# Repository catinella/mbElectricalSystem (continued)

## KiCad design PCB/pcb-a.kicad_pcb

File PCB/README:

#-------------------------------------------------------------------------------------------------------------------------------
   __  __       _             _     _ _          _____ _           _        _           _   ____            _                 
  |  \/  | ___ | |_ ___  _ __| |__ (_) | _____  | ____| | ___  ___| |_ _ __(_) ___ __ _| | / ___| _   _ ___| |_ ___ _ __ ___  
  | |\/| |/ _ \| __/ _ \| '__| '_ \| | |/ / _ \ |  _| | |/ _ \/ __| __| '__| |/ __/ _` | | \___ \| | | / __| __/ _ \ '_ ` _ \ 
  | |  | | (_) | || (_) | |  | |_) | |   <  __/ | |___| |  __/ (__| |_| |  | | (_| (_| | |  ___) | |_| \__ \ ||  __/ | | | | |
  |_|  |_|\___/ \__\___/|_|  |_.__/|_|_|\_\___| |_____|_|\___|\___|\__|_|  |_|\___\__,_|_| |____/ \__, |___/\__\___|_| |_| |_|
                                                                                                  |___/                       
#-------------------------------------------------------------------------------------------------------------------------------

Description:
	This folder contains all files you need to get you own PCB.

Files:
	LICENSE.txt                 This project is covered by the GPL-3. Please, read that file for further information
	Makefile                    It allow you to create the files (es. Gebber) needed to produce the PCB (KiCAD-7)
	kicad_symbols               This folder contains all components definitions not provided by KiCAD by default
	pcb-a                       All files belong to the PCB-a
	pcb-b                       All files belong to the PCB-b
	starter_key_plug            Schema to show the key-plug internals

Internals:
	The power astage was originally implemented with BJT transistors, but as my colleague usually say "we are no more in the
	90' age".  For this reason I have designed a new PCB-B using MOSfet technology

	+---------+--------------------------------+--------------------------------+
	| BC817   | VCE=0.2V IC=800mA              | BJT NPN                        |
	| IRF4905 | RDS=20mOhm ID=50A VGS=[-2..-4] | P-Channel MOSfet enhancement   |
	+---------+--------------------------------+--------------------------------+

Devices building:
	About the PCBs creation I have used the MD srl company service. So, in order to create a copy, you can contact the company
	(https://www.mdsrl.it) and use the following order numbers, it will allow you to save some money.
		+-----------------+-----------+----------+---------------+
		|       PCB       |   GIT TAG | MD order |     Price     |
		+-----------------+-----------+----------+---------------+
		| pcb-a.kicad_pcb | r-2.2.4-0 |  81552   | 18.9 euro * 2 |
		+-----------------+-----------+--------------------------+
		| pcb-b.kicad_pcb | r-2.2.4-b |  882813  | 36.5 euro * 2 |
		+-----------------+-----------+--------------------------+

	PCB building details:
	=====================
	In order to get a more vibrations resistant circuit,  I suggest you to print it on a 3.2mm high plate
	
	[!] It you are using Linux, you too, remember that the PCB building company will require you a ZIP file (not GZIP).
	    So, after the fabric-files generation use the following command to create the zip file:
	    	zip -r <archive name> <data folder name>

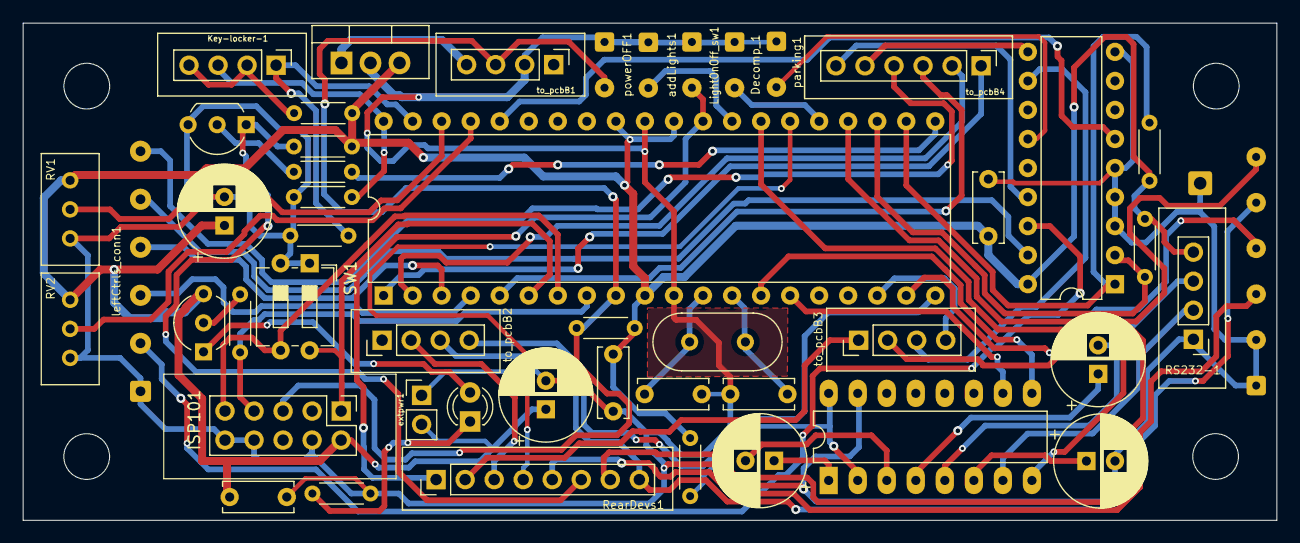
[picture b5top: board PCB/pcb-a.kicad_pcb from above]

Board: 2 copper layers, 109.7 x 43.5 mm, 49 parts (0 on the bottom side), 58 nets.

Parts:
C1: 100uf; CP_Radial_D8.0mm_P2.50mm
C2, C9, C10: 100nF; C_Disc_D6.0mm_W2.5mm_P5.00mm
C3: 15pf; C_Disc_D6.0mm_W2.5mm_P5.00mm
C4: 15pF; C_Disc_D6.0mm_W2.5mm_P5.00mm
C5, C6, C8: 1uf; CP_Radial_D8.0mm_P2.50mm
C7: 50uf; CP_Radial_D8.0mm_P2.50mm
D1: LED; LED_D3.0mm
Decomp_1: Conn_01x02; SolderWire-0.15sqmm_1x02_P4mm_D0.5mm_OD1.5mm
ISP101: ISP10 Connector; PinHeader_2x05_P2.54mm_Vertical
Key-locker-1: Conn_01x04; PinHeader_1x04_P2.54mm_Vertical
LightOnOff_sw1: Conn_01x02; SolderWire-0.15sqmm_1x02_P4mm_D0.5mm_OD1.5mm
Q1: BC327; TO-92_Inline_Wide
Q3: BC337; TO-92_Inline_Wide
R1, R3, R4: 1K; R_Axial_DIN0204_L3.6mm_D1.6mm_P5.08mm_Horizontal
R2, R7, R8: 10K; R_Axial_DIN0204_L3.6mm_D1.6mm_P5.08mm_Horizontal
R5, R10: 2K; R_Axial_DIN0204_L3.6mm_D1.6mm_P5.08mm_Horizontal
R6: 100K; R_Axial_DIN0204_L3.6mm_D1.6mm_P5.08mm_Horizontal
R9: 5K; R_Axial_DIN0204_L3.6mm_D1.6mm_P5.08mm_Horizontal
R11: 20; R_Axial_DIN0204_L3.6mm_D1.6mm_P5.08mm_Horizontal
RS232-1: Conn_01x04; PinHeader_1x04_P2.54mm_Vertical
RV1, RV2: 10K; Potentiometer_Bourns_3296W_Vertical
RearDevs1: Conn_01x08; PinHeader_1x08_P2.54mm_Vertical
SW1: config; SW_DIP_SPSTx02_Slide_6.7x6.64mm_W7.62mm_P2.54mm_LowProfile
U1: MCP23008-xP; DIP-18_W7.62mm
U2: MAX232I; CERDIP-16_W7.62mm_SideBrazed_LongPads
U3: L7805; TO-220-3_Vertical
U4: ATmega16L-8P; DIP-40_W15.24mm
Y1: 8Mhz; Crystal_HC49-U_Vertical
addLights1: Conn_01x02; SolderWire-0.15sqmm_1x02_P4mm_D0.5mm_OD1.5mm
extpwr1: Conn_01x02; PinHeader_1x02_P2.54mm_Vertical
leftCtrls-faston1: Conn_01x01; SolderWire-0.5sqmm_1x01_D0.9mm_OD2.1mm
leftCtrls_conn1: Conn_01x06; SolderWire-0.25sqmm_1x06_P4.2mm_D0.65mm_OD1.7mm
parking1: Conn_01x02; SolderWire-0.15sqmm_1x02_P4mm_D0.5mm_OD1.5mm
powerOFF1: Conn_01x02; SolderWire-0.15sqmm_1x02_P4mm_D0.5mm_OD1.5mm
rightCtrls_conn1: Conn_01x06; SolderWire-0.15sqmm_1x06_P4mm_D0.5mm_OD1.5mm
to_pcbB1, to_pcbB2, to_pcbB3: Conn_01x04; PinHeader_1x04_P2.54mm_Vertical
to_pcbB4: Conn_01x06; PinHeader_1x06_P2.54mm_Vertical

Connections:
5V: C1.1, C2.1, C7.1, C9.1, C10.2, ISP101.2, Q1.3 (E), R1.1, R2.1, R5.1, R6.2, R10.1, R11.1, RS232-1.4, RV1.1, RV2.1, U1.18 (VDD), U3.3 (OUT), U4.10 (VCC), U4.30 (AVCC), U4.32 (AREF), extpwr1.2
GND: C1.2, C2.2, C3.2, C4.2, C7.2, C8.2, C9.2, C10.1, Decomp_1.1, ISP101.4, ISP101.8, ISP101.10, LightOnOff_sw1.1, Q3.3 (E), R3.2, R4.2, R9.2, RS232-1.1, RV1.3, RV2.3, SW1.1, SW1.2, U1.3 (A2), U1.4 (A1), U1.5 (A0), U1.9 (VSS), U2.15 (GND), U3.2 (GND), U4.11 (GND), U4.31 (GND), addLights1.1, extpwr1.1, leftCtrls-faston1.1, leftCtrls_conn1.1, parking1.1, powerOFF1.1, rightCtrls_conn1.1, rightCtrls_conn1.2, to_pcbB1.2
unnamed: D1.2 (A), Q1.1 (C)
unnamed: D1.1 (K), R9.1
unnamed: ISP101.1, SW1.4, U4.6 (PB5)
unnamed: ISP101.7, R8.2, U4.8 (PB7)
unnamed: ISP101.9, SW1.3, U4.7 (PB6)
unnamed: Key-locker-1.2, Key-locker-1.4, R1.2
unnamed: Q1.2 (B), R8.1
unnamed: Q3.2 (B), R7.1
unnamed: RS232-1.2, U2.7 (T2OUT)
unnamed: RS232-1.3, U2.8 (R2IN)
unnamed: R10.2, U1.1 (SCL), U4.22 (PC0)
unnamed: R5.2, U1.2 (SDA), U4.23 (PC1)
unnamed: U1.6 (~RESET), U4.36 (PA4)
unnamed: C5.1, U2.1 (C1+)
unnamed: C5.2, U2.3 (C1-)
unnamed: C6.1, U2.4 (C2+)
unnamed: C6.2, U2.5 (C2-)
unnamed: R11.2, U2.2 (VS+), U2.16 (VCC)
unnamed: C8.1, U2.6 (VS-)
unnamed: U3.1 (IN), to_pcbB1.4
unnamed: RV1.2, U4.38 (PA2)
unnamed: RV2.2, U4.37 (PA3)
unnamed: C3.1, U4.13 (XTAL1), Y1.2
unnamed: C4.1, U4.12 (XTAL2), Y1.1
c_RS232_RXD: U2.9 (R2OUT), U4.14 (PD0)
c_RS232_TXT: U2.10 (T2IN), U4.15 (PD1)
c_brakeSwitch: RearDevs1.5, rightCtrls_conn1.3
c_engineOFF: RearDevs1.8, rightCtrls_conn1.5, to_pcbB2.3
c_horn: leftCtrls_conn1.6, to_pcbB4.4
c_leftArrow: RearDevs1.2, to_pcbB3.1
c_neutral: RearDevs1.7, U4.27 (PC5), to_pcbB3.2
c_rearLight: LightOnOff_sw1.2, RearDevs1.1, U4.29 (PC7)
c_rightArrow: RearDevs1.3, to_pcbB2.2
c_startEngine: Q3.1 (C), R6.1, RearDevs1.6
i_Vx1: Key-locker-1.3, R3.1, U4.40 (PA0)
i_Vx2: Key-locker-1.1, R4.1, U4.39 (PA1)
i_addLight: U4.28 (PC6), addLights1.2
i_bykeStand: RearDevs1.4, U4.26 (PC4)
i_decompr: Decomp_1.2, U4.25 (PC3)
i_downLight: U4.4 (PB3), leftCtrls_conn1.3
i_engineON: U4.24 (PC2), rightCtrls_conn1.6
i_leftArrow: U1.16 (GP6), leftCtrls_conn1.2
i_parking: U1.13 (GP3), parking1.2
i_powerOFF: ISP101.5, R2.2, U4.9 (~RESET), powerOFF1.2, to_pcbB1.3
i_rightArrow: U1.17 (GP7), leftCtrls_conn1.5
i_startButton: U4.19 (PD5), rightCtrls_conn1.4
i_upLight: U4.3 (PB2), leftCtrls_conn1.4
o_addLight: U4.5 (PB4), to_pcbB4.3
o_downLight: U4.1 (PB0), to_pcbB4.1
o_engineON: U4.20 (PD6), to_pcbB2.4
o_engineReady: U1.11 (GP1), to_pcbB3.3
o_keepAlive: U4.18 (PD4), to_pcbB3.4
o_leftArrow: U1.15 (GP5), to_pcbB4.6
o_rightArrow: U1.10 (GP0), to_pcbB4.5
o_startEngine: R7.2, U4.21 (PD7)
o_upLight: U4.2 (PB1), to_pcbB4.2

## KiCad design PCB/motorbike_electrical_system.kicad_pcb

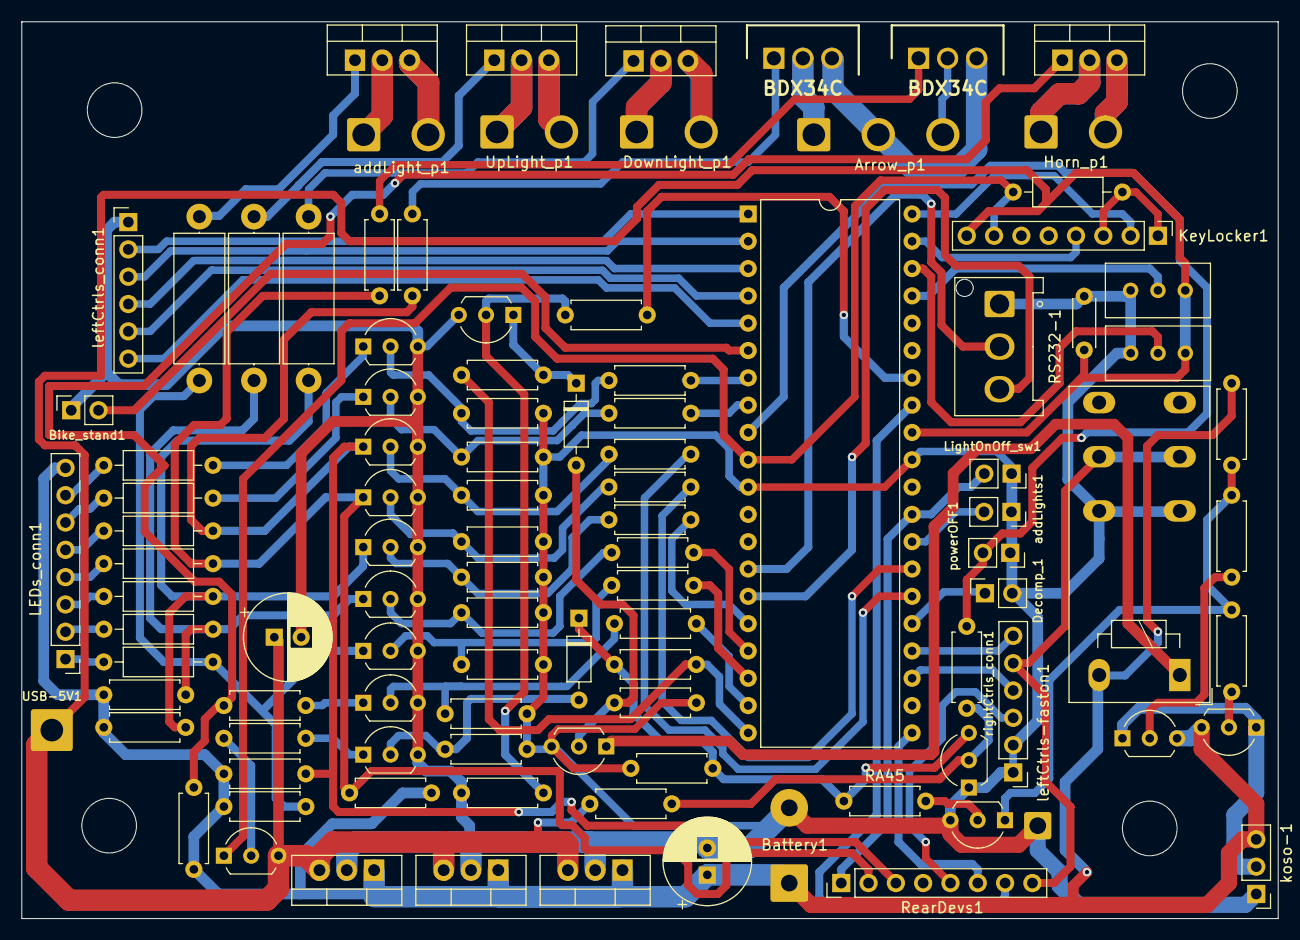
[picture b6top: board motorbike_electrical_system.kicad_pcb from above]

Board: 2 copper layers, 116.9 x 83.4 mm, 104 parts (0 on the bottom side), 91 nets.

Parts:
Arrow_p1: Conn_01x03; SolderWire-1.5sqmm_1x03_P6mm_D1.7mm_OD3mm
Battery1: Conn_01x02; SolderWire-0.75sqmm_1x02_P7mm_D1.25mm_OD3.5mm
Bike_stand1: Conn_01x02; PinSocket_1x02_P2.54mm_Vertical
C1, C9: C_Polarized_Small; CP_Radial_D8.0mm_P2.50mm
C2: 100nF; C_Disc_D4.3mm_W1.9mm_P5.00mm
D3, D4: 2V; D_DO-35_SOD27_P7.62mm_Horizontal
Decomp_1: Conn_01x02; PinSocket_1x02_P2.54mm_Vertical
DownLight_p1: Conn_01x02; SolderWire-1.5sqmm_1x02_P6mm_D1.7mm_OD3mm
Horn_p1: Conn_01x02; SolderWire-1.5sqmm_1x02_P6mm_D1.7mm_OD3mm
IC2, IC3: BDX34C; TO270P460X1020X2008-3P
K1: RT42xxxx; Relay_DPDT_Schrack-RT2-FormC_RM5mm
KeyLocker1: Conn_01x08; PinHeader_1x08_P2.54mm_Vertical
LEDs_conn1: Conn_01x08; PinHeader_1x08_P2.54mm_Vertical
LightOnOff_sw1: Conn_01x02; PinSocket_1x02_P2.54mm_Vertical
Q1, Q2, Q14, Q15: D45VH10; TO-220-3_Vertical
Q3, Q4, Q5, Q6, Q7, Q8, Q9, Q10, Q11, Q13, Q16, Q17: BC337; TO-92L_Inline_Wide
Q12, Q18, Q19, Q20: BC327; TO-92L_Inline_Wide
R1: 1K; R_Axial_DIN0207_L6.3mm_D2.5mm_P10.16mm_Horizontal
RA1, RA2, RA3, RA4, RA5, RA6, RA9: 0; R_Axial_DIN0207_L6.3mm_D2.5mm_P10.16mm_Horizontal
RA7: 1K; R_Axial_DIN0207_L6.3mm_D2.5mm_P7.62mm_Horizontal
RA8, RA41: 4K; R_Axial_DIN0207_L6.3mm_D2.5mm_P7.62mm_Horizontal
RA10, RA11, RA12: 240; R_Axial_DIN0414_L11.9mm_D4.5mm_P15.24mm_Horizontal
RA13, RA14: 8K; R_Axial_DIN0207_L6.3mm_D2.5mm_P7.62mm_Horizontal
RA15: 240; R_Axial_DIN0207_L6.3mm_D2.5mm_P7.62mm_Horizontal
RA16, RA17, RA18, RA19, RA20, RA21, RA22, RA23: 5K; R_Axial_DIN0207_L6.3mm_D2.5mm_P7.62mm_Horizontal
RA24, RA25, RA26, RA27, RA28, RA30, RA31, RA32, RA34, RA35, RA36, RA37, RA38, RA39, RA40, RA42, RA43, RA44, RA48, RA49: 100K; R_Axial_DIN0207_L6.3mm_D2.5mm_P7.62mm_Horizontal
RA29, RA33, RA45: 10K; R_Axial_DIN0207_L6.3mm_D2.5mm_P7.62mm_Horizontal
RA46, RA47: 3K; R_Axial_DIN0207_L6.3mm_D2.5mm_P7.62mm_Horizontal
RS232-1: Conn_01x03; Hirose_DF63M-3P-3.96DSA_1x03_P3.96mm_Vertical
RV1, RV2: 10K; Potentiometer_Bourns_3296W_Vertical
RearDevs1: Conn_01x08; PinHeader_1x08_P2.54mm_Vertical
U1, U2, U3: L7805; TO-220-3_Vertical
U4: ATmega16L-8P; DIP-40_W15.24mm
USB-5V1: Conn_01x01; SolderWire-1.5sqmm_1x01_D1.7mm_OD3.9mm
UpLight_p1: Conn_01x02; SolderWire-1.5sqmm_1x02_P6mm_D1.7mm_OD3mm
addLight_p1: Conn_01x02; SolderWire-1.5sqmm_1x02_P6mm_D1.7mm_OD3mm
addLights1: Conn_01x02; PinSocket_1x02_P2.54mm_Vertical
koso-1: Conn_01x03; PinHeader_1x03_P2.54mm_Vertical
leftCtrls-faston1: Conn_01x01; SolderWire-0.75sqmm_1x01_D1.25mm_OD2.3mm
leftCtrls_conn1: Conn_01x06; PinHeader_1x06_P2.54mm_Vertical
powerOFF1: Conn_01x02; PinSocket_1x02_P2.54mm_Vertical
rightCtrls_conn1: Conn_01x06; PinHeader_1x06_P2.54mm_Vertical

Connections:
+5V: C1.1, C2.1, KeyLocker1.8, Q12.3 (E), RA44.1, RV1.1, RV2.1, U1.3 (OUT), U2.3 (OUT), U3.3 (OUT), U4.32 (AREF), USB-5V1.1
+12V: Battery1.1, C9.1, K1.A2, LEDs_conn1.8, Q19.3 (E), Q20.3 (E), RA24.1, RA25.1, RA26.1, RA27.1, RA28.1, RA42.1, RA49.2, U1.1 (IN), U2.1 (IN), U3.1 (IN), koso-1.3
GND: Battery1.2, Bike_stand1.1, C1.2, C2.2, C9.2, Decomp_1.2, K1.12, K1.22, LightOnOff_sw1.1, Q3.3 (E), Q4.3 (E), Q5.3 (E), Q6.3 (E), Q7.3 (E), Q8.3 (E), Q9.3 (E), Q10.3 (E), Q11.3 (E), Q13.3 (E), Q16.3 (E), Q17.3 (E), Q18.1 (C), RA30.2, RA31.2, RA32.2, RA34.2, RA35.2, RA36.2, RA37.2, RA38.2, RA39.2, RA40.2, RA43.1, RA48.2, RS232-1.1, RV1.3, RV2.3, U1.2 (GND), U2.2 (GND), U3.2 (GND), U4.11 (GND), U4.31 (GND), addLights1.1, koso-1.1, leftCtrls-faston1.1, leftCtrls_conn1.1, powerOFF1.1, rightCtrls_conn1.1, rightCtrls_conn1.2
unnamed: Arrow_p1.1, IC3.2 (C)
unnamed: Arrow_p1.2, IC2.3 (E), IC3.3 (E)
unnamed: Arrow_p1.3, IC2.2 (C)
unnamed: D3.1 (K), Q17.1 (C), RA41.1
unnamed: D3.2 (A), Q13.2 (B), RA31.1
unnamed: D4.1 (K), Q18.3 (E), RA8.1, RA45.1, RA48.1
unnamed: D4.2 (A), Q11.2 (B), RA30.1
unnamed: DownLight_p1.1, Q14.2
unnamed: DownLight_p1.2, Q14.3
unnamed: Horn_p1.1, Q15.2
unnamed: Horn_p1.2, Q15.3
unnamed: IC2.1 (B), RA13.2
unnamed: IC3.1 (B), RA14.2
unnamed: K1.A1, Q13.1 (C)
unnamed: KeyLocker1.1, KeyLocker1.3, R1.2
unnamed: LEDs_conn1.1, RA1.2
unnamed: LEDs_conn1.2, RA2.2
unnamed: LEDs_conn1.3, RA3.2
unnamed: LEDs_conn1.4, RA4.2
unnamed: LEDs_conn1.5, RA5.2
unnamed: LEDs_conn1.6, RA6.2
unnamed: LEDs_conn1.7, RA9.2
unnamed: Q1.1, RA10.2
unnamed: Q1.2, addLight_p1.1
unnamed: Q1.3, addLight_p1.2
unnamed: Q2.1, RA11.2
unnamed: Q2.2, UpLight_p1.1
unnamed: Q2.3, UpLight_p1.2
unnamed: Q3.1 (C), RA1.1, RA10.1, RA24.2
unnamed: Q3.2 (B), RA22.1, RA34.1
unnamed: Q4.1 (C), RA2.1, RA11.1, RA25.2
unnamed: Q4.2 (B), RA21.1, RA35.1
unnamed: Q5.1 (C), RA3.1, RA12.1, RA26.2
unnamed: Q5.2 (B), RA20.1, RA36.1
unnamed: Q6.2 (B), RA19.1, RA37.1
unnamed: Q7.2 (B), RA18.1, RA38.1
unnamed: Q8.1 (C), RA6.1
unnamed: Q8.2 (B), RA17.1, RA39.1
unnamed: Q9.1 (C), RA15.1
unnamed: Q9.2 (B), RA23.1, RA32.1
unnamed: Q10.1 (C), RA9.1
unnamed: Q10.2 (B), RA16.1, RA40.1
unnamed: Q11.1 (C), RA7.1
unnamed: Q12.2 (B), RA7.2
unnamed: Q14.1, RA12.2
unnamed: Q15.1, RA15.2, RA42.2
unnamed: Q16.1 (C), RA46.2, RA47.2, RA49.1
unnamed: Q16.2 (B), RA45.2
unnamed: Q17.2 (B), RA33.1, RA43.2
unnamed: Q18.2 (B), RA29.1, RA44.2
unnamed: Q19.1 (C), Q20.1 (C), koso-1.2
unnamed: Q19.2 (B), RA46.1
unnamed: Q20.2 (B), RA47.1
unnamed: RS232-1.2, U4.14 (PD0)
unnamed: RV1.2, U4.38 (PA2)
unnamed: RV2.2, U4.37 (PA3)
unnamed: RS232-1.3, U4.15 (PD1)
c_brakeSwitch: RearDevs1.5, rightCtrls_conn1.3
c_engineOFF: K1.11, K1.21, RearDevs1.8, rightCtrls_conn1.5
c_leftArrow: Q6.1 (C), RA4.1, RA13.1, RA27.2, RearDevs1.2
c_rearLight: LightOnOff_sw1.2, RearDevs1.1, U4.29 (PC7)
c_rightArrow: Q7.1 (C), RA5.1, RA14.1, RA28.2, RearDevs1.3
i_Vx1: KeyLocker1.2, U4.40 (PA0)
i_Vx2: KeyLocker1.4, U4.39 (PA1)
i_addLight: U4.28 (PC6), addLights1.2
i_bykeStand: Bike_stand1.2, U4.6 (PB5)
i_decompr: Decomp_1.1, U4.25 (PC3)
i_downLight: U4.2 (PB1), leftCtrls_conn1.3
i_engineON: U4.24 (PC2), rightCtrls_conn1.6
i_horn: U4.5 (PB4), leftCtrls_conn1.6
i_leftArrow: U4.1 (PB0), leftCtrls_conn1.2
i_neutral: RearDevs1.7, U4.33 (PA7)
i_powerOFF: RA29.2, U4.9 (~RESET), powerOFF1.2
i_rightArrow: U4.4 (PB3), leftCtrls_conn1.5
i_startButton: U4.23 (PC1), rightCtrls_conn1.4
i_upLight: U4.3 (PB2), leftCtrls_conn1.4
o_addLight: RA22.2, U4.18 (PD4)
o_downLight: RA20.2, U4.16 (PD2)
o_engineOFF: RA33.2, U4.34 (PA6)
o_engineReady: RA16.2, U4.7 (PB6)
o_horn: RA23.2, U4.19 (PD5)
o_keepAlive: RA8.2, RA41.2, U4.20 (PD6)
o_leftArrow: RA19.2, U4.27 (PC5)
o_neutral: RA17.2, U4.8 (PB7)
o_rightArrow: RA18.2, U4.26 (PC4)
o_startEngine: RearDevs1.6, U4.21 (PD7)
o_upLight: RA21.2, U4.17 (PD3)
tempPower: KeyLocker1.7, Q12.1 (C), R1.1, U4.10 (VCC)

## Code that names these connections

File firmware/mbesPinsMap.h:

/*------------------------------------------------------------------------------------------------------------------------------
//
//  __  __       _             _     _ _          _____ _           _        _           _   ____            _                 
// |  \/  | ___ | |_ ___  _ __| |__ (_) | _____  | ____| | ___  ___| |_ _ __(_) ___ __ _| | / ___| _   _ ___| |_ ___ _ __ ___  
// | |\/| |/ _ \| __/ _ \| '__| '_ \| | |/ / _ \ |  _| | |/ _ \/ __| __| '__| |/ __/ _` | | \___ \| | | / __| __/ _ \ '_ ` _ \
// | |  | | (_) | || (_) | |  | |_) | |   <  __/ | |___| |  __/ (__| |_| |  | | (_| (_| | |  ___) | |_| \__ \ ||  __/ | | | | |
// |_|  |_|\___/ \__\___/|_|  |_.__/|_|_|\_\___| |_____|_|\___|\___|\__|_|  |_|\___\__,_|_| |____/ \__, |___/\__\___|_| |_| |_|
//                                                                                                 |___/                       
//
// File:   mbesPinsMap.h
//
// Author: Silvano Catinella <catinella@yahoo.com>
//
//
//	Symbol description:
//		+---------------+------------------+-----------------------------------------------------+
//		|     Symbol    |    Plug/link     |      Description                                    |
//		+---------------+------------------+-----------------------------------------------------+
//		| i_VX1         | resistors-key    | first voltage value                                 |
//		| i_VX2         |                  | second  "       "                                   |
//		+---------------+------------------+-----------------------------------------------------+
//		| i_VY1         |  internal link   | first voltage reference                             |
//		| i_VY2         |                  | second  "         "                                 |
//		+---------------+------------------+-----------------------------------------------------+
//		| i_NEUTRAL     | from gearbox     | it is 0 when the gear is in neutral position        |
//		+---------------+------------------+-----------------------------------------------------+
//		| i_DECOMPRESS  | from decompress. | it is 0 when decompressor has been pushes           |
//		+---------------+------------------+-----------------------------------------------------+
//		| o_KEEPALIVE   | internal only    | it keeps the system on when you unplug the key      |
//		+---------------+------------------+-----------------------------------------------------+
//		| i_LEFTARROW   |                  | left turn blinking indicator switch                 |
//		| i_CLUTCH      |                  |                                     |
//		| i_UPLIGHT     | left controls    | dazzling beam command                               |
//		| i_RIGHTARROW  |                  | right turn blinking indicator switch                |
//		| i_HORN        |                  | horn button                                         |
//		+---------------+------------------+-----------------------------------------------------+
//		| i_BIKESTAND   | from bikestand   | it is 0 when the bike is placed on the stand        |
//		+---------------+------------------+-----------------------------------------------------+
//		| i_STARTBUTTON |                  | the tipical motorbike engine start button           |
//		| i_BRAKESWITCH | right controls   | the switch on the front brake command               |
//		| i_ENGINEON    |                  | the on/off engine switch in on-position             |
//		+---------------+------------------+-----------------------------------------------------+
//		| i_ADDLIGHT    | from ext. switch | additional high power light                         |
//		+---------------+------------------+-----------------------------------------------------+
//		| i_LIGHTONOFF  | from ext. switch | it turns on the normal lights (low/dazzling beam)   |
//		+---------------+------------------+-----------------------------------------------------+
//		| o_STARTENGINE | rear mtb. side   | it activates the (NO) engine-relay                  |
//		+---------------+------------------+-----------------------------------------------------+
//		| o_ENGINEREADY |                  |                                                     |
//		| o_NEUTRAL     |                  |                                                     |
//		| o_RIGHTARROW  |   cockpit LED    |                                                     |
//		| o_LEFTARROW   | indicators and   |                                                     |
//		| o_DOWNLIGHT   |    services      |                                                     |
//		| o_UPLIGHT     |                  |                                                     |
//		| o_ADDLIGHT    |                  |                                                     |
//		| o_HORN        |                  |                                                     |
//		+---------------+------------------+-----------------------------------------------------+
//
// License:
//	Copyright (C) 2023 Silvano Catinella <catinella@yahoo.com>
//
//	This program is free software: you can redistribute it and/or modify it under the terms of the GNU General Public
//	License as published by the Free Software Foundation, either version 3 of the License, or (at your option) any later
//	version.
//
//	This program is distributed in the hope that it will be useful, but WITHOUT ANY WARRANTY; without even the implied
//	warranty of MERCHANTABILITY or FITNESS FOR A PARTICULAR PURPOSE. See the GNU General Public License for more details.
//
//	You should have received a copy of the GNU General Public License along with this program. If not, see
//		<https://www.gnu.org/licenses/gpl-3.0.txt>.
//
------------------------------------------------------------------------------------------------------------------------------*/
#ifndef MBESPINSMAP
#define MBESPINSMAP

//
// PINs declaration
//

#define i_VX1          "A0"
#define i_VX2          "A1"
#define i_VY1          "A2"
#define i_VY2          "A3"
#define o_MCPDEVRESET  "A4"
// ==== available ==== "A5"
#define i_SELCONFIG    "A6"
#define i_CONFIG       "A7"


#define o_DOWNLIGHT    "B0"
#define o_UPLIGHT      "B1"
#define i_UPLIGHT      "B2"
#define i_CLUTCH       "B3"
#define o_ADDLIGHT     "B4"
// ===== ISP =====     "B5"
// ===== ISP =====     "B6"
// ===== ISP =====     "B7"


// ====== I2C ======   "C0"
// ====== I2C ======   "C1"
#define i_ENGINEON     "C2"
#define i_DECOMPRESS   "C3"
#define i_BYKESTAND    "C4"
#define i_NEUTRAL      "C5"
#define i_ADDLIGHT     "C6"
#define i_LIGHTONOFF   "C7"


// === RXD UART ===    "D0"
// === TXD UART ===    "D1"
// ==== available ==== "D2"
// ==== available ==== "D3"
#define o_KEEPALIVE    "D4"
#define i_STARTBUTTON  "D5"
#define o_ENGINEON     "D6"
#define o_STARTENGINE  "D7"


#define o_RIGHTARROW   "00"
#define o_ENGINEREADY  "01"
#define o_NEUTRAL      "02"
#define o_HORN         "03"
#define i_HORN         "04"
#define o_LEFTARROW    "05"
#define i_LEFTARROW    "06"
#define i_RIGHTARROW   "07"


// Number of used analog input
#define ACHANS_NUMBER   4

#endif

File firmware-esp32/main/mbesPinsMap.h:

/*------------------------------------------------------------------------------------------------------------------------------
//
//  __  __       _             _     _ _          _____ _           _        _           _   ____            _                 
// |  \/  | ___ | |_ ___  _ __| |__ (_) | _____  | ____| | ___  ___| |_ _ __(_) ___ __ _| | / ___| _   _ ___| |_ ___ _ __ ___  
// | |\/| |/ _ \| __/ _ \| '__| '_ \| | |/ / _ \ |  _| | |/ _ \/ __| __| '__| |/ __/ _` | | \___ \| | | / __| __/ _ \ '_ ` _ \
// | |  | | (_) | || (_) | |  | |_) | |   <  __/ | |___| |  __/ (__| |_| |  | | (_| (_| | |  ___) | |_| \__ \ ||  __/ | | | | |
// |_|  |_|\___/ \__\___/|_|  |_.__/|_|_|\_\___| |_____|_|\___|\___|\__|_|  |_|\___\__,_|_| |____/ \__, |___/\__\___|_| |_| |_|
//                                                                                                 |___/                       
//
// File:   mbesPinsMap.h
//
// Author: Silvano Catinella <catinella@yahoo.com>
//
//
//	Symbol description:
//		+---------------+------------------+-----------------------------------------------------+
//		|     Symbol    |    Plug/link     |      Description                                    |
//		+---------------+------------------+-----------------------------------------------------+
//		| i_VX1         | resistors-key    | first voltage value                                 |
//		| i_VX2         |                  | second  "       "                                   |
//		+---------------+------------------+-----------------------------------------------------+
//		| i_NEUTRAL     | from gearbox     | it is 0 when the gear is in neutral position        |
//		+---------------+------------------+-----------------------------------------------------+
//		| i_DECOMPRESS  | from decompress. | it is 0 when decompressor has been pushes           |
//		+---------------+------------------+-----------------------------------------------------+
//		| o_KEEPALIVE   | internal only    | it keeps the system on when you unplug the key      |
//		+---------------+------------------+-----------------------------------------------------+
//		| i_BIKESTAND   | from bikestand   | it is 0 when the bike is placed on the stand        |
//		+---------------+------------------+-----------------------------------------------------+
//		| i_ADDLIGHT    | from ext. switch | additional high power light                         |
//		+---------------+------------------+-----------------------------------------------------+
//		| i_LIGHTONOFF  | from ext. switch | it turns on the normal lights (low/dazzling beam)   |
//		+---------------+------------------+-----------------------------------------------------+
//		| o_STARTENGINE | rear mtb. side   | it activates the (NO) engine-relay                  |
//		+---------------+------------------+-----------------------------------------------------+
//		| i_LEFTARROW   |                  | left turn blinking indicator switch                 |
//		| i_RIGHTARROW  |                  | right turn blinking indicator switch                |
//		| i_DOWNLIGHT   | left controls    |                                                     |
//		| i_UPLIGHT     |                  | dazzling beam command                               |
//		| i_HORN        |                  | horn button                                         |
//		| i_CLUTCH      |                  | 0 means the engine is NOT connected to the wheels   |
//		+---------------+------------------+-----------------------------------------------------+
//		| i_STARTBUTTON |                  | the tipical motorbike engine start button           |
//		| i_BRAKESWITCH | right controls   | the switch on the front brake command               |
//		| i_ENGINEON    |                  | the on/off engine switch in on-position             |
//		+---------------+------------------+-----------------------------------------------------+
//		| o_ENGINEREADY |                  |                                                     |
//		| o_NEUTRAL     |                  |                                                     |
//		| o_RIGHTARROW  |   cockpit LED    |                                                     |
//		| o_LEFTARROW   | indicators and   |                                                     |
//		| o_DOWNLIGHT   |    services      |                                                     |
//		| o_UPLIGHT     |                  |                                                     |
//		| o_ADDLIGHT    |                  |                                                     |
//		| o_HORN        |                  |                                                     |
//		+---------------+------------------+-----------------------------------------------------+
//
// License:
//	Copyright (C) 2023 Silvano Catinella <catinella@yahoo.com>
//
//	This program is free software: you can redistribute it and/or modify it under the terms of the GNU General Public
//	License as published by the Free Software Foundation, either version 3 of the License, or (at your option) any later
//	version.
//
//	This program is distributed in the hope that it will be useful, but WITHOUT ANY WARRANTY; without even the implied
//	warranty of MERCHANTABILITY or FITNESS FOR A PARTICULAR PURPOSE. See the GNU General Public License for more details.
//
//	You should have received a copy of the GNU General Public License along with this program. If not, see
//		<https://www.gnu.org/licenses/gpl-3.0.txt>.
//
------------------------------------------------------------------------------------------------------------------------------*/
#ifndef MBESPINSMAP
#define MBESPINSMAP

//
// PINs declaration
//

#define i_STARTBUTTON    GPIO_NUM_0
#define i_VX1            ADC_CHANNEL_0
#define i_VX2            ADC_CHANNEL_1
// ==== available ====   GPIO3/ADC1_CH2
// ==== available ====   GPIO4/ADC1_CH3
// ==== available ====   GPIO5/ADC1_CH4
// ==== available ====   GPIO6/ADC1_CH5
// ==== available ====   GPIO7/ADC1_CH6
#define i_LEFTARROW      GPIO_NUM_8
#define i_CONF1          GPIO_NUM_9
#define i_CONF2          GPIO_NUM_10
#define i_NEUTRAL        GPIO_NUM_11
#define o_KEEPALIVE      GPIO_NUM_12
#define o_ENGINEREADY    GPIO_NUM_13
#define o_NEUTRAL        GPIO_NUM_14
#define i_DECOMPRESS     GPIO_NUM_15
#define o_ENGINEON       GPIO_NUM_16
#define o_UPLIGHT        GPIO_NUM_17
#define o_LEFTARROW      GPIO_NUM_18
// !!!!                  USB/GPIO_NUM_19
// !!!!                  USB/GPIO_NUM_20
#define i_ADDLIGHT       GPIO_NUM_21
#define i_ENGINEON       GPIO_NUM_26
#define i_RIGHTARROW     GPIO_NUM_33
#define o_ADDLIGHT       GPIO_NUM_34
#define i_DOWNLIGHT      GPIO_NUM_35
#define i_UPLIGHT        GPIO_NUM_36
// ==== available ====   GPIO_NUM_37   Many problems met to use it as output, in the ESP32 it was just an input pin
#define o_DOWNLIGHT      GPIO_NUM_38
#define o_RIGHTARROW     GPIO_NUM_39
#define o_STARTENGINE    GPIO_NUM_40
#define i_CLUTCH         GPIO_NUM_41
#define i_BIKESTAND      GPIO_NUM_42
// (TX) DON'T USE IT !!! GPIO_NUM_43   System freezing
// (RX) DON'T USE IT !!! GPIO_NUM_44   Firmware uploading failure
#define i_LIGHTONOFF     GPIO_NUM_45
// ==== available ====   GPIO_NUM_46    Only as input push & pull 3V

#endif

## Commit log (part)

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2024-09-06 I2C read/write operations optimization
2024-09-06 Updates to the new mbesUtilities module version
2024-09-11 Pin-header connectors adjustment
    The main idea to mount the two pcb-A on the pcbB has been dropped, because the result is a too much chatic one and I realized that
    wires welder on the top is a dangerous solution, they can create unwanted contacts and short-circuits... So, I choise to place the
    two PCB beside. So, in order to get a more ordered and clean solution, I am using flat cables instead wires, and pin-header
    connectors instead of welding them directly. I foung good connectors where every female-plug is blocked in its male-socket. But,
    they are available just for even numbers of pins. For this reason, I have adjusted all the pin-header connectors and their
    positions.
2024-09-13 Components positions adjustment
2024-09-19 Refactoring: sub-sheets re-ordering
    conn_to_pcbb.kicad_sch and mbes_rear_connector.kicad_sch sheets content have been copied into the mbes_inputs.kicad_sch sheets.
    This file has been renamed to mbes_pcbA_connectors.kicad_sch
2024-09-20 20 Ohm resistor added for MAX232
    I got overheating experience on that chip. So, I looked for some info on internet. But I found just a post that suggest to add
    the resistor to prevent capacitor dircharge trouble. I have tried the solution and it looks like function very well. But don't
    ask me why!!! :-(
2024-09-23 New debug console app
    For an unknown reason the old perl debugConsole no more functions: is whows corrupted characters. It is strange consifering I
    have not modified it!!! However, because I already wanted to rewrite it in C, it is the right moment to do it
2024-09-26 Fixes for normal-logs area
2024-09-27 The C version has replaced Perl one
    The Perl version started to have problems: it read corrupted chars from the serial console. I have used that version for long time
    without problems and I don't know why it started to get corrupted chars. However, rewriting it in C was one of the items in my todo
    list, so I take the opportunity to do it. In fact Perl version has been always too slow, and the screen was no stable.
    The C version is really better.
    A special huge thanks to Brian Kernighan & Dennis Ritchie
    (You are one of the stars that drive my path, always)
2024-09-28 I2CBUS_RESET section added
    In this session, the MCP23008 get a reset, then it is re-initialized
2024-09-29 Refactoring
    The main file's function used to checkout the symbol used for a pin, has been moved to this external module.
2024-09-30 Fixes for stringBuilder_put() and stringBuilder_get()
    This version has been fully tested with valgrind too
2024-09-30 No special characters are allowed
    I have added aso some deep memory cleaning. It should not be dtrictly needed, but avoid Valgrind's wornings
2024-10-01 Partial rewritten
    When it's possible, FSM is better than many flags :-)
2024-10-02 o_NEUTRAL is connected directly to the led
2024-10-03 Metal box for DR350 with KTM forks and rally fairing
2024-10-03 PCB size reduction
2024-10-04 External power connector, and one 100nF cap. added
2024-10-04 Another merging operation from ATmega16__dualPCB
2024-10-05 Input and output pins together
2024-10-06 Dependences added
2024-10-07 Test for ESP32's timer()
2024-10-09 Debug monitor to keep track of MCU's pins status
    Module ported by the remotes/origin/ATmega16__dualPCB branch
2024-10-09 Header files path missing fixed
2024-10-09 Comments and logs added
2024-10-10 Fix for iInputInterface_new() and comments removed
    (many cut not all) comment used for debug have been removed
    This version has been fully tested, it function very well
2024-10-10 debugConsole porting has been started ;-)
2024-10-11 stringBuilder_put() refactored
    It has been rewritten to manage the escape sequences too
2024-10-11 BUILDER_NOSCAPECODES symbol switch implemented
2024-10-12 External (Makefile.conf) file inclusion
    In order to make the building process configuration easier, I opted to use ab external file
2024-10-12 Makefile.conf masked
2024-10-12 Small fix and many error-codes added
2024-10-13 basic utilities for ascii printing
2024-10-13 Simple test
2024-10-13 Incoherent names fixed
2024-10-14 Enhancement
    In order to get ordered and clean code, the CheckPinStatus() function has been splitted in pinDef_get() and pinDef_free(). These
    function have been moved into the pinToSymbol module, in this way all platform depemdent changes are located in one single
    header file.
2024-10-14 fix for _iatoi()
2024-10-15 small changes
2024-10-15 APIs have been rewritten
    It provides two APIs with the skill to adjust itselves to the target architeture
2024-10-15 Preprocessor debug message added
2024-10-16 werror.h including (-I<path>) option added
2024-10-16 For ESP-IDF's bug it can't be handled as component
2024-10-16 included into the main .gitignore file
2024-10-16 Small fix for iInputInterface_get()
2024-10-17 Fix for _moduleDB_get()
    Shared memory has been marked as volatile resource
2024-10-17 Many fixes (100% building errors free)
2024-10-18 moduleDB building added
2024-10-18 Fixes for _iInputInterface_updateAll()
2024-10-19 Many fixes
    - blinker() missing initialization fixed
    - app_main() nissing fixed
    - A/D converter wrong configuration fixes
2024-10-21 small change
2024-10-22 More stable implementation
2024-10-22 Source file switching management added
2024-10-24 Refactoring
    In order to avoid pin insormation loosing, I changed API approach: no more function to send data directly to debug-console, now,
    the lib provides two wrapper to the input/output system api. Replacing these with the debug-console wrappers, you cannot loose
    pin status!!
2024-10-24 Important chages!! Never use the GPIO_NUM_43/44!!!!!
2024-10-24 Fix for keepTrack_setGPIO()
2024-10-24 i_LIGHTONOFF pin swapped with i_STARTBUTTON one
    The pin-0 (where is connected i_LIGHTONOFF) is used by the MCU to select which boot it has to perform. It means, if you turn-on
    your motorbike with the light turned-on, then the motorbike will be frozen. I have swapped with i_STARTBUTTON, because nobody
    turned-on his netal-horse with the start button already pushed!!!!
2024-10-27 Old files replaced.
    They have been merged for error
2024-11-01 Enhancements
    - the four single-lines connectors to the MPU has been replaced by two dual-lines connectors. It is a great advantage in the
    PCB mounting, because the two-lines ones does not require to be welder!! The connectors are mounted using special pillers.
    - Because turn-indicator led-light use less then 100mA current, I have replaced the MOSFETS with BC327 NPN BJTs. In this way
    I have semoved the fuse. In fact the transistor is set to make flow just ((12/7K)*130) 223mA and it should not release more
    then 300mA in short-ciruit situation. So the fuse is not more needed.
2025-01-02 Usual git-ignore rules file
2025-01-04 Fixes and updates
    This version will be tested soon. It is fully implemented with THT devices using ESP32-S2 DevKit
2025-01-06 Enhancement for direction-indicators circuit
    To make the circuit completely safe, I have added MSMF050-2 restatable-fuses to protect it vs short-circuits events.
    In order to prevent PNP transistors damages, I have also added a 3 Ohm 0.5W resistor composed by four 1206 SMD componets
2025-03-31 ustomixed colder-wire connector added
    This connector allow me to use 0.75 sqmm cables in more comsortable way
2025-05-21 hanges and fix
    - The R6 and R8 pull-up resistors have been removed. I will use internal ones
    - The J2 connector position has been moved
2025-05-29 Fix and update
    - Warning sybol with wrong code fixed
    - WERRCODE_ERROR_FROMEXTLIB symbol added
2025-05-29 Wrong documentation fixed
    Old references to the Perl version have been removed
2025-05-29 Enhancement: log removing in normal mode
2025-06-02 Fix and enhancement
    - i_BIKESTAND symbol fixed
    - NOAUTH symbol management added
2025-06-05 Doc updating...
    Description of NODLSWITCH symbol has been added
2025-06-06 Enhancement for parse_config()
    parse_config() dunction can manage comment lines, now
2025-06-06 Small size problem fixed
2025-07-07 Footprint updating
2025-07-29 Fix: o_KEEPALIVE wrong behavior in NOAUTH mode
2025-07-30 Change: flat box
    Because the two pcb could fit in the box horizontally, I have redraw an easier to produce box. But I have to check for the
    box status after the welding
2025-08-01 Measures added
2025-08-03 Fix: parking mode after bootstrap
    In order to avoid unwanted parking mode selection, the commands sequence MUST keep selected for a time period.
2025-08-04 Small enhancement: all components on the same side
2025-08-07 Enhancement: easier to weller version
2025-08-07 Fix: the internal size was wrong for dual-PCB version
    In this version you need a further small box for the key socket, the system-off buttan and the engine-ready led
2026-02-25 Components sizes and positions optimizing
    - 3-pins Koso's comnnector has been substituted with a more standard 4-pins one
    - One resistor has been moved to free space for EngReady_led connector
2026-02-26 Small fixes
    - Floating BC817's base fixed
    - EngReady_LED connector orientation fixed
2026-02-27 Connectors changing
    In order to reuse the already used cables, all the input signal connectors have been changed from solder-wires-sockets to pin-header connectors.
2026-03-02 onnectors number reducing
    Because clucth lever switch is always placed in the left side of the handle-bar, I added the pin to the left-controls connector.
    The 6-pins connector has been substituted by an 8-pins one.
    In this way I got two advantages:
    - I have reduced the command cables in the upside of the PCB
    - The left and right controls connectors are different, now
2026-03-03 Updates, fixes, and new format
2026-03-04 Porting from main branch
2026-03-04 README file in mark down format, with images
2026-03-10 threaded clothespins habe been replaced by threaded square bars
2026-03-15 ravgFilter module loading added
2026-03-15 RAVG deeping level tuning
2026-03-15 Description added for KEYSETTING symbol
2026-03-18 Wrong electric track size fixed
2026-03-24 Small enhancements
2026-03-25 The external box for the circuit on the DR350 rear side
    It should be placed on the space used by the fuse box originally.
2026-03-26 Text size tuned
2026-03-26 Motorbike rear side power stage PCB
2026-03-29 Size reducing (48.3mm x 34.5mm)
2026-03-30 wrong position fixed
2026-03-30 New README format
2026-03-30 More generic documentation moved to the up folder README file
2026-03-30 Documentation for electrical system box building process
2026-03-31 External power connector is now used for rear power stage
2026-03-31 Enhancements and size reduction
    - Because the day-light needs just low current (<=500 mA), it no more uses the passive fuse. It has been replaced by a
    MSMF050-2 electronic fuse. Less passive fuses means less electric wires, then less chaos!
    - A better components space distribution has reduced the PCB size (40.00mm x 90.11mm)
2026-04-01 InternalComps layer added bottom holes size changed
2026-04-03 Rimozione resistenge sui gates e aggiunta diodo fly-back
    PCB size reducing
2026-04-03 Updates for new PCB(c) sizes
2026-04-03 common README.md file
2026-04-06 Merge from ESP32__dualPCB branch
    - DownLight: external fuse replaced by internal automatic one, wire connector replaced by 2.54 pin-header
    - The resistor between FET's gate and NPN's collector has been removed
2026-04-06 insideComps layer added
2026-04-08 Fly back diode added to relay
2026-04-08 PCB-C merging from main
2026-04-09 More specific README.md files inside the sub-dirs
2026-04-09 Standard README.md file
    The info belong to the ../Connectors.txt file, have been included in the README.md file
2026-04-10 Better disposition
2026-04-10 Language fixes
2026-04-14 Small optimization
2026-04-15 Merging from main
    Key authentication physical references removed
2026-04-15 New section for motorcycle's key setting and language fixes
2026-04-16 Mounting holes changed
    Original mounting holes size was 3.2mm, because I wanted to thread them 4MA. But the screws would have worked on ((10-4)/2)
    aluminium 3mm, and it would be a bad solution. So, I have changed the supports thant now have 2 4.2mm holes in one side and
    one (same size) hole in the middle of the other lateral side. In this way I can user screwns and nuts.
2026-04-21 Fix for 2.3.1 section: Wrong data type
2026-04-21 WERRCODE_WARNING_TESTFAILED and WERRCODE_ERROR_NVSIOFAILED symbols added
2026-04-21 authKey dependence added
2026-04-21 Screw holes size changed (5MA --> 4MA)
2026-04-27 Fixes and enhancements
2026-04-27 Utility firmware to show the plugget resistive key's values
2026-04-28 First release (building errors free)
2026-04-28 Fixes for the 2.3.1 section and 2.3.2 section added
